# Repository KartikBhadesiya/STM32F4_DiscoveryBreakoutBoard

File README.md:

# STM32F4_DiscoveryBreakoutBoard
Here is .sch and .brd file in EAGLE for STM32f4 Discovery Breakout Board

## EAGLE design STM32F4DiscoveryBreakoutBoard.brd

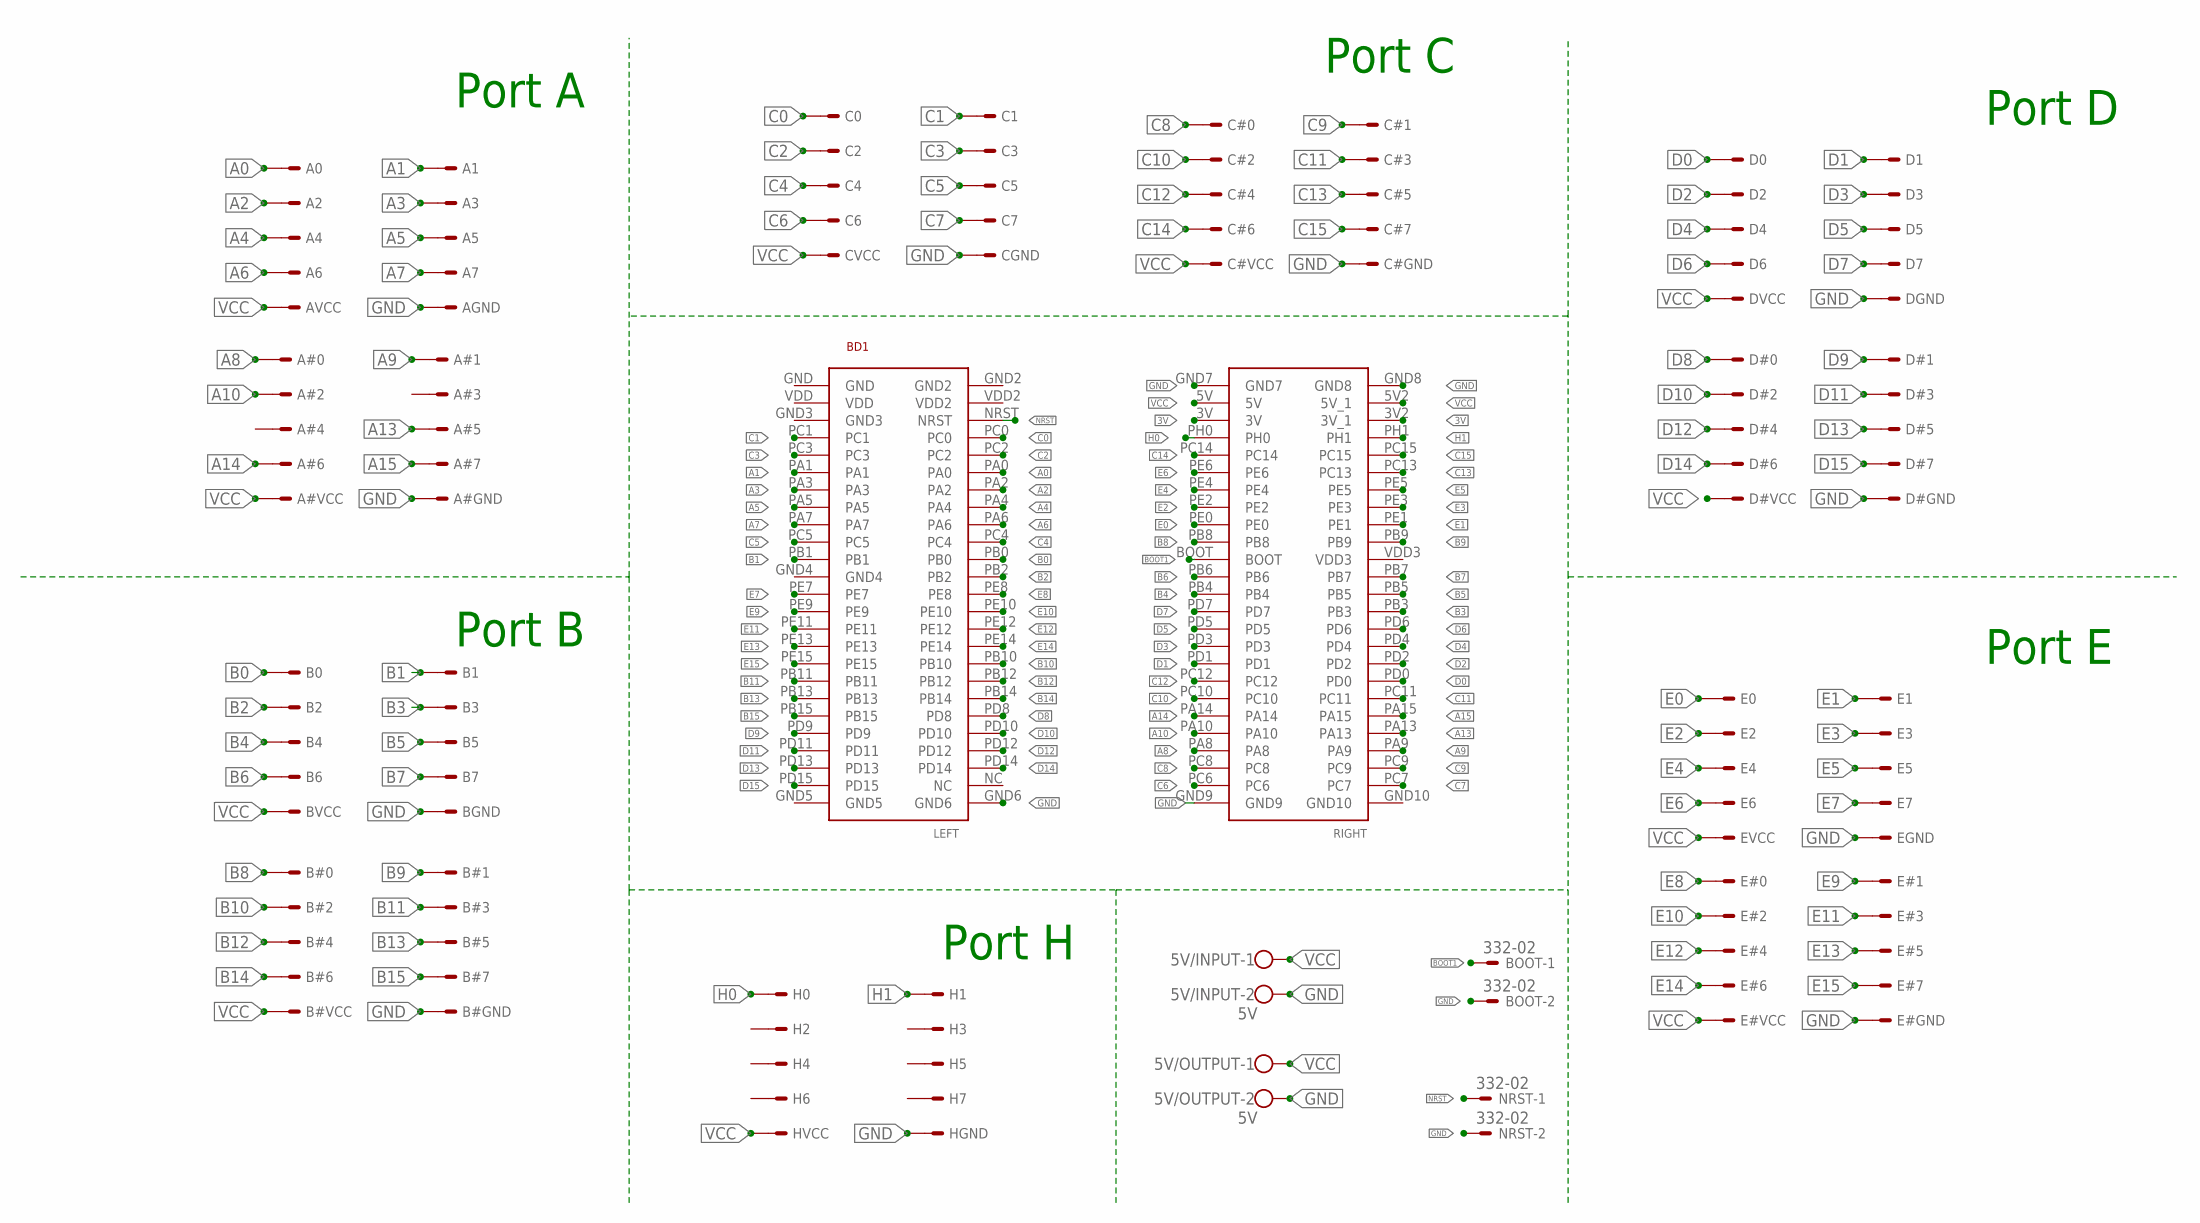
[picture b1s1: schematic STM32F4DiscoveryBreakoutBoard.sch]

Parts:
5V/INPUT, 5V/OUTPUT: 5V; W237-102
A: FR1; 057-010-1
A#: FR1; 057-010-1
B: FR1; 057-010-1
B#: FR1; 057-010-1
BD1: STM32F4-DISCOVERY; STM32F407VG
BOOT: 332-02
C: FR1; 057-010-1
C#: FR1; 057-010-1
D: FR1; 057-010-1
D#: FR1; 057-010-1
E: FR1; 057-010-1
E#: FR1; 057-010-1
H: FR1; 057-010-1
NRST: 332-02

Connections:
3V: BD1.3V, BD1.3V2 (3V_1)
A0: A.0, BD1.PA0
A1: A.1, BD1.PA1
A2: A.2, BD1.PA2
A3: A.3, BD1.PA3
A4: A.4, BD1.PA4
A5: A.5, BD1.PA5
A6: A.6, BD1.PA6
A7: A.7, BD1.PA7
A8: A#.0, BD1.PA8
A9: A#.1, BD1.PA9
A10: A#.2, BD1.PA10
A13: A#.5, BD1.PA13
A14: A#.6, BD1.PA14
A15: A#.7, BD1.PA15
B0: B.0, BD1.PB0
B1: B.1, BD1.PB1
B2: B.2, BD1.PB2
B3: B.3, BD1.PB3
B4: B.4, BD1.PB4
B5: B.5, BD1.PB5
B6: B.6, BD1.PB6
B7: B.7, BD1.PB7
B8: B#.0, BD1.PB8
B9: B#.1, BD1.PB9
B10: B#.2, BD1.PB10
B11: B#.3, BD1.PB11
B12: B#.4, BD1.PB12
B13: B#.5, BD1.PB13
B14: B#.6, BD1.PB14
B15: B#.7, BD1.PB15
BOOT1: BD1.BOOT, BOOT.1
C0: BD1.PC0, C.0
C1: BD1.PC1, C.1
C2: BD1.PC2, C.2
C3: BD1.PC3, C.3
C4: BD1.PC4, C.4
C5: BD1.PC5, C.5
C6: BD1.PC6, C.6
C7: BD1.PC7, C.7
C8: BD1.PC8, C#.0
C9: BD1.PC9, C#.1
C10: BD1.PC10, C#.2
C11: BD1.PC11, C#.3
C12: BD1.PC12, C#.4
C13: BD1.PC13, C#.5
C14: BD1.PC14, C#.6
C15: BD1.PC15, C#.7
D0: BD1.PD0, D.0
D1: BD1.PD1, D.1
D2: BD1.PD2, D.2
D3: BD1.PD3, D.3
D4: BD1.PD4, D.4
D5: BD1.PD5, D.5
D6: BD1.PD6, D.6
D7: BD1.PD7, D.7
D8: BD1.PD8, D#.0
D9: BD1.PD9, D#.1
D10: BD1.PD10, D#.2
D11: BD1.PD11, D#.3
D12: BD1.PD12, D#.4
D13: BD1.PD13, D#.5
D14: BD1.PD14, D#.6
D15: BD1.PD15, D#.7
E0: BD1.PE0, E.0
E1: BD1.PE1, E.1
E2: BD1.PE2, E.2
E3: BD1.PE3, E.3
E4: BD1.PE4, E.4
E5: BD1.PE5, E.5
E6: BD1.PE6, E.6
E7: BD1.PE7, E.7
E8: BD1.PE8, E#.0
E9: BD1.PE9, E#.1
E10: BD1.PE10, E#.2
E11: BD1.PE11, E#.3
E12: BD1.PE12, E#.4
E13: BD1.PE13, E#.5
E14: BD1.PE14, E#.6
E15: BD1.PE15, E#.7
GND: 5V/INPUT.2, 5V/OUTPUT.2, A.GND, A#.GND, B.GND, B#.GND, BD1.GND6, BD1.GND7, BD1.GND8, BD1.GND9, BOOT.2, C.GND, C#.GND, D.GND, D#.GND, E.GND, E#.GND, H.GND, NRST.2
H0: BD1.PH0, H.0
H1: BD1.PH1, H.1
NRST: BD1.NRST, NRST.1
VCC: 5V/INPUT.1, 5V/OUTPUT.1, A.VCC, A#.VCC, B.VCC, B#.VCC, BD1.5V, BD1.5V2 (5V_1), C.VCC, C#.VCC, D.VCC, D#.VCC, E.VCC, E#.VCC, H.VCC

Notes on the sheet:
Port A
Port B
Port C
Port D
Port E
Port H

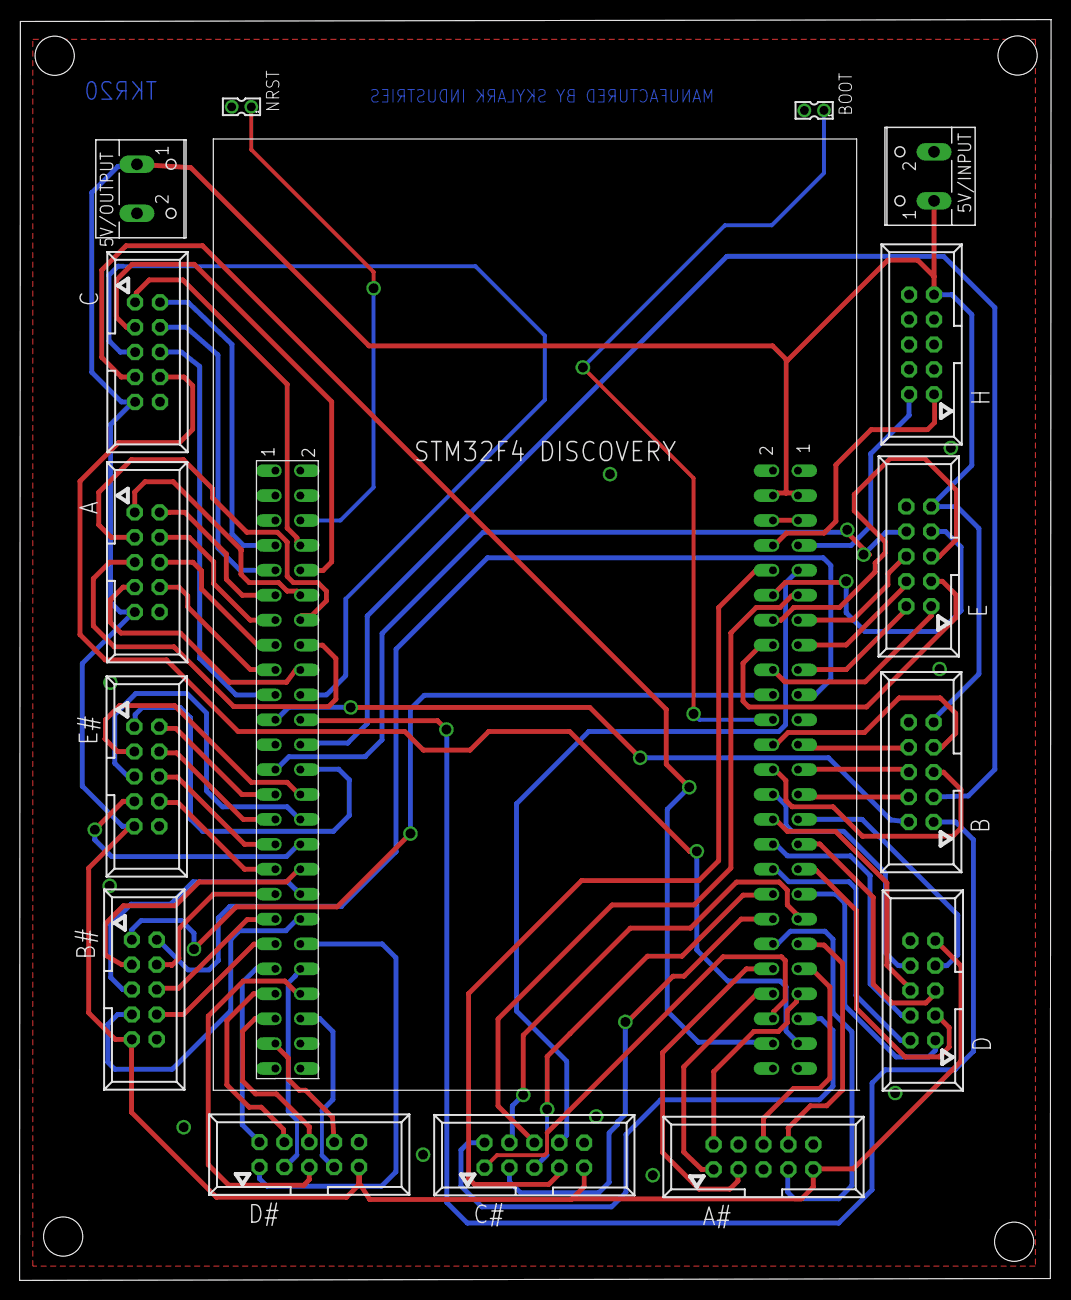
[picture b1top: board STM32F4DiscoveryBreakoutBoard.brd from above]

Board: 2 copper layers, 105.2 x 128.6 mm, 16 parts (0 on the bottom side), 85 nets.
